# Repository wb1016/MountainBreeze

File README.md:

# Mountain Breeze

> Ergonomics meets Productivity.

## Introduction

"Mountain Breeze" is a tented split mechanical keyboard with a column-staggered layout. With a focus on productivity, Breeze features a full 6x4 alphanumeric layout, arrow keys, and an extra 6 key cluster for typing and coding.

Learn more at: [www.afternoonlabs.com/mountain-breeze](https://www.afternoonlabs.com/mountain-breeze)

## Features

* Tented Split Ergonomics
* Productivity Cluster for Typing and Coding
* Wireless-First, Fits a Giant Battery
* Built-in On/Off Switch
* Open-source PCB design for easy modifications
* Hotswap MX or Choc Sockets, MX Sockets Built-in!
* Diodes Built-in, No Diode Soldering Required
* Columnar Stagger
* Arrow Keys!

## Support us

Enjoying the Breeze? [Buy me a beer](https://www.buymeacoffee.com/Afternoonlabs).

## Contribution

Contributions are encouraged! Whether it's bug fixes, new features, or even simple feedback, everything helps in making the project better.

1. Fork the Project
2. Create your Feature Branch (`git checkout -b feature/SomeFeature`)
3. Commit your Changes (`git commit -m 'Adding SomeFeature'`)
4. Push to the Branch (`git push origin feature/SomeFeature`)
5. Open a Pull Request

## License

Anyone can use this project for personal use. Distributed under the MIT License. See `LICENSE` for more information.

Vendors interested in selling the Breeze, please contact us below.

The use of "Afternoon Labs" is protected under copyright law. Unauthorized use without express permission from "Afternoon Labs", is prohibited.

## Contact

Join our [Discord Server](https://discord.gg/9nsApe3GvG).

Afternoon Labs - [hi@afternoonlabs.com](mailto:hi@afternoonlabs.com)

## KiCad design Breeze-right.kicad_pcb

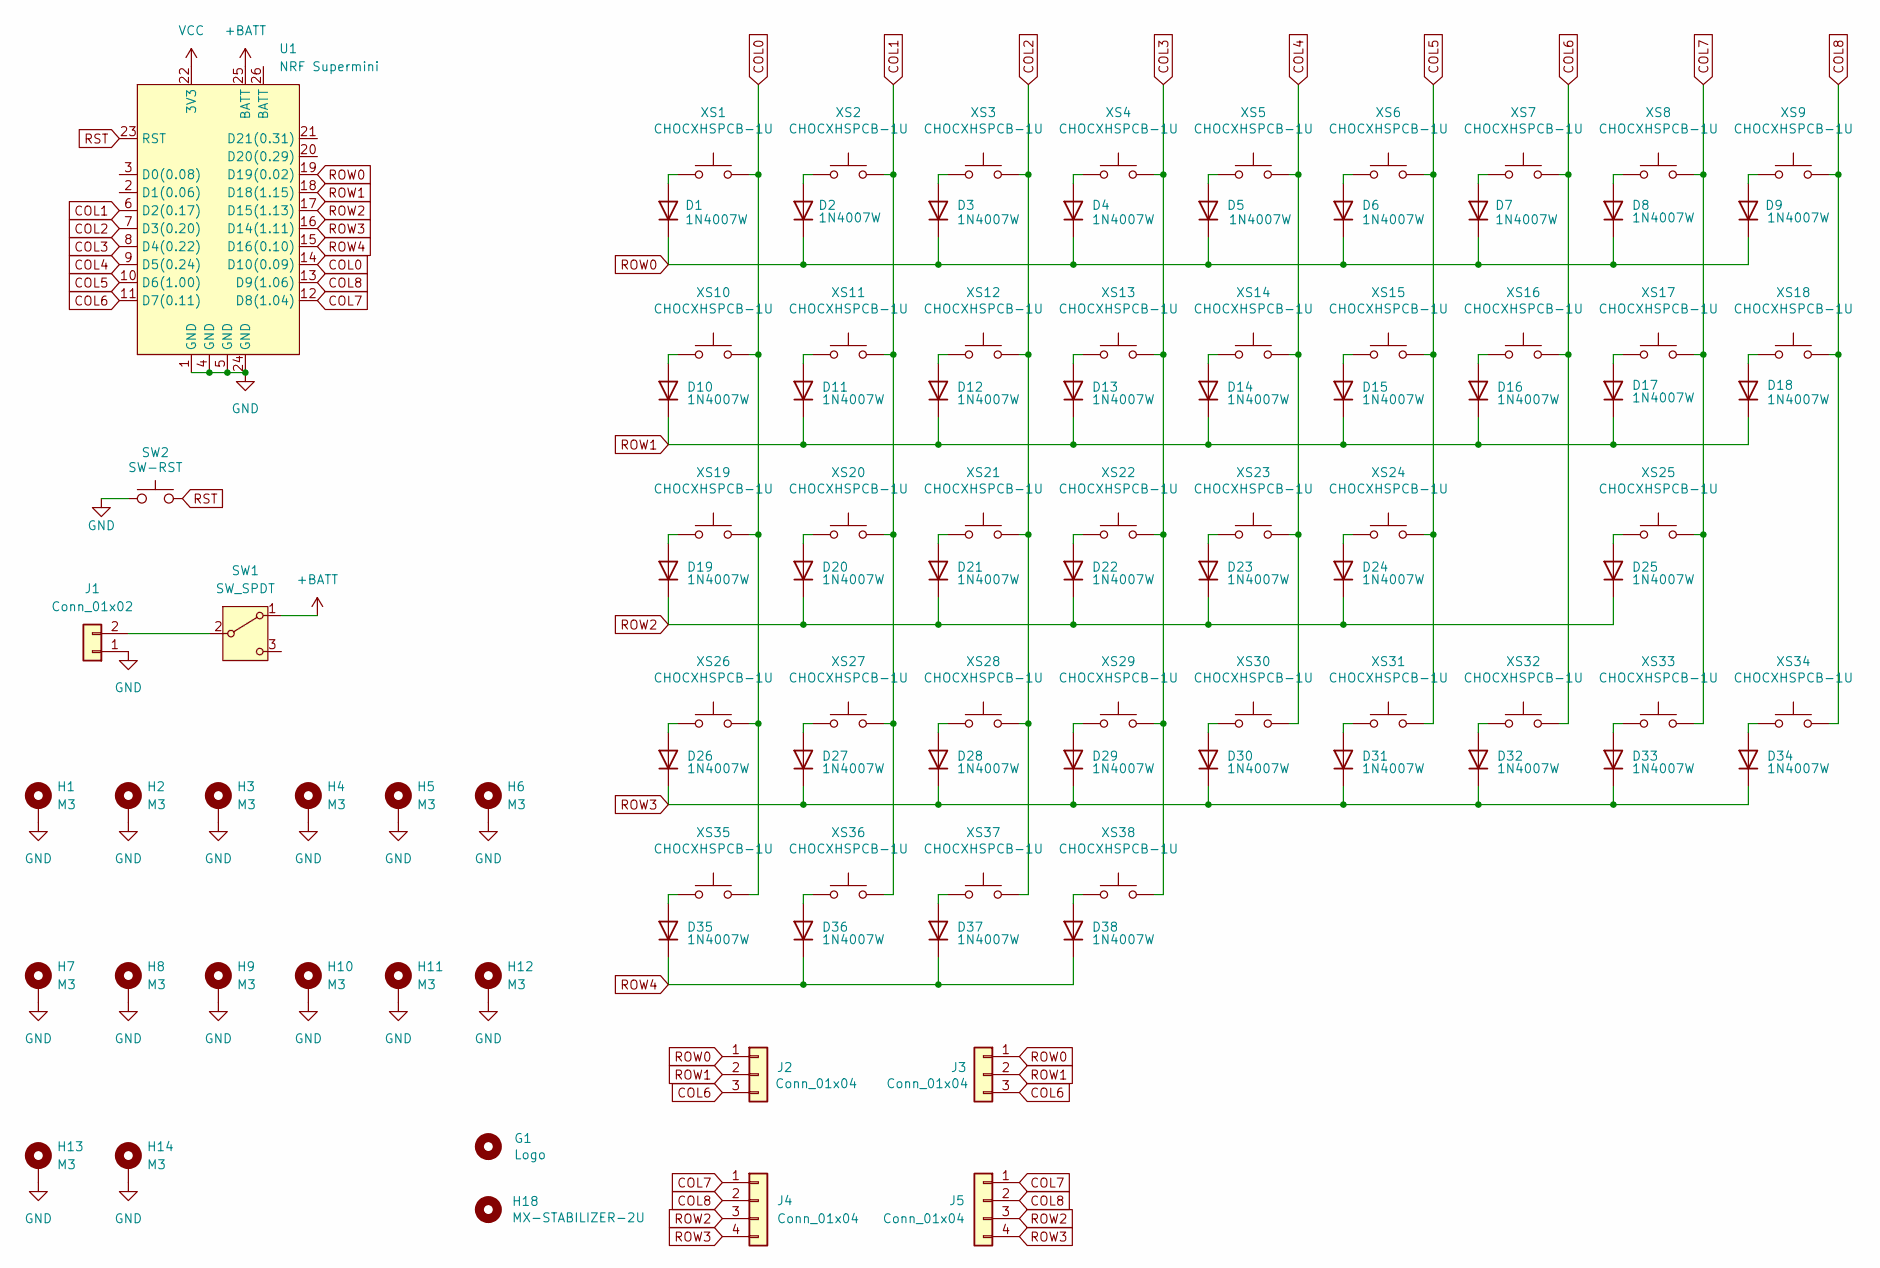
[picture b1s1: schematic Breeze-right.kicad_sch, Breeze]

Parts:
D1, D2, D3, D4, D5, D6, D7, D8, D9, D10, D11, D12, D13, D14, D15, D16, D17, D18, D19, D20, D21, D22, D23, D24, D25, D26, D27, D28, D29, D30, D31, D32, D33, D34, D35, D36, D37, D38: 1N4007W; SOD-123FL_L2.7-W1.8-LS3.7-RD; LCSC C64898
G1: Logo; logo
H1, H3, H4, H6, H7, H9, H10, H11, H12, H13, H14: M3; MountingHole_3.2mm_M3_ISO7380_Pad
H2, H5, H8: M3; MountingHole_3.2mm_M3_ISO7380_Pad_TopOnly
H18: MX-STABILIZER-2U; Stabilizer_MX_2u
J1: Conn_01x02; BATT_PADS
J2, J3: Conn_01x04; PinHeader_1x03_P2.54mm_Vertical
J4, J5: Conn_01x04; PinHeader_1x04_P2.54mm_Vertical
SW1: SW_SPDT; SS12D00; LCSC C145861
SW2: SW-RST; SW_SPST_TL3342; LCSC C2886897
U1: NRF Supermini; NRF_Supermini
XS1, XS2, XS3, XS4, XS5, XS6, XS7, XS8, XS9, XS10, XS11, XS12, XS13, XS14, XS15, XS16, XS17, XS18, XS19, XS20, XS21, XS22, XS23, XS24, XS25, XS26, XS27, XS28, XS29, XS30, XS31, XS32, XS33, XS34, XS35, XS36, XS37, XS38: CHOCXHSPCB-1U; MX_Choc_Hotswap_1-Sided; LCSC C41430893

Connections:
+BATT: SW1.1 (A), U1.25 (BATT)
COL0: U1.14 (D10(0.09)), XS1.2, XS10.2, XS19.2, XS26.2, XS35.2
COL1: U1.6 (D2(0.17)), XS2.2, XS11.2, XS20.2, XS27.2, XS36.2
COL2: U1.7 (D3(0.20)), XS3.2, XS12.2, XS21.2, XS28.2, XS37.2
COL3: U1.8 (D4(0.22)), XS4.2, XS13.2, XS22.2, XS29.2, XS38.2
COL4: U1.9 (D5(0.24)), XS5.2, XS14.2, XS23.2, XS30.2
COL5: U1.10 (D6(1.00)), XS6.2, XS15.2, XS24.2, XS31.2
COL6: J2.3, J3.3, U1.11 (D7(0.11)), XS7.2, XS16.2, XS32.2
COL7: J4.1, J5.1, U1.12 (D8(1.04)), XS8.2, XS17.2, XS25.2, XS33.2
COL8: J4.2, J5.2, U1.13 (D9(1.06)), XS9.2, XS18.2, XS34.2
GND: H1.1, H2.1, H3.1, H4.1, H5.1, H6.1, H7.1, H8.1, H9.1, H10.1, H11.1, H12.1, H13.1, H14.1, J1.1, SW2.1, U1.1 (GND), U1.4 (GND), U1.5 (GND), U1.24 (GND)
unnamed: D1.2 (A), XS1.1
unnamed: D2.2 (A), XS2.1
unnamed: D3.2 (A), XS3.1
unnamed: D4.2 (A), XS4.1
unnamed: D5.2 (A), XS5.1
unnamed: D6.2 (A), XS6.1
unnamed: D7.2 (A), XS7.1
unnamed: D8.2 (A), XS8.1
unnamed: D9.2 (A), XS9.1
unnamed: D10.2 (A), XS10.1
unnamed: D11.2 (A), XS11.1
unnamed: D12.2 (A), XS12.1
unnamed: D13.2 (A), XS13.1
unnamed: D14.2 (A), XS14.1
unnamed: D15.2 (A), XS15.1
unnamed: D16.2 (A), XS16.1
unnamed: D17.2 (A), XS17.1
unnamed: D18.2 (A), XS18.1
unnamed: D19.2 (A), XS19.1
unnamed: D20.2 (A), XS20.1
unnamed: D21.2 (A), XS21.1
unnamed: D22.2 (A), XS22.1
unnamed: D23.2 (A), XS23.1
unnamed: D24.2 (A), XS24.1
unnamed: D25.2 (A), XS25.1
unnamed: D26.2 (A), XS26.1
unnamed: D27.2 (A), XS27.1
unnamed: D28.2 (A), XS28.1
unnamed: D29.2 (A), XS29.1
unnamed: D30.2 (A), XS30.1
unnamed: D31.2 (A), XS31.1
unnamed: D32.2 (A), XS32.1
unnamed: D33.2 (A), XS33.1
unnamed: D34.2 (A), XS34.1
unnamed: D35.2 (A), XS35.1
unnamed: D36.2 (A), XS36.1
unnamed: D37.2 (A), XS37.1
unnamed: D38.2 (A), XS38.1
unnamed: J1.2, SW1.2 (B)
ROW0: D1.1 (K), D2.1 (K), D3.1 (K), D4.1 (K), D5.1 (K), D6.1 (K), D7.1 (K), D8.1 (K), D9.1 (K), J2.1, J3.1, U1.19 (D19(0.02))
ROW1: D10.1 (K), D11.1 (K), D12.1 (K), D13.1 (K), D14.1 (K), D15.1 (K), D16.1 (K), D17.1 (K), D18.1 (K), J2.2, J3.2, U1.18 (D18(1.15))
ROW2: D19.1 (K), D20.1 (K), D21.1 (K), D22.1 (K), D23.1 (K), D24.1 (K), D25.1 (K), J4.3, J5.3, U1.17 (D15(1.13))
ROW3: D26.1 (K), D27.1 (K), D28.1 (K), D29.1 (K), D30.1 (K), D31.1 (K), D32.1 (K), D33.1 (K), D34.1 (K), J4.4, J5.4, U1.16 (D14(1.11))
ROW4: D35.1 (K), D36.1 (K), D37.1 (K), D38.1 (K), U1.15 (D16(0.10))
RST: SW2.2, U1.23 (RST)
VCC: U1.22 (3V3)

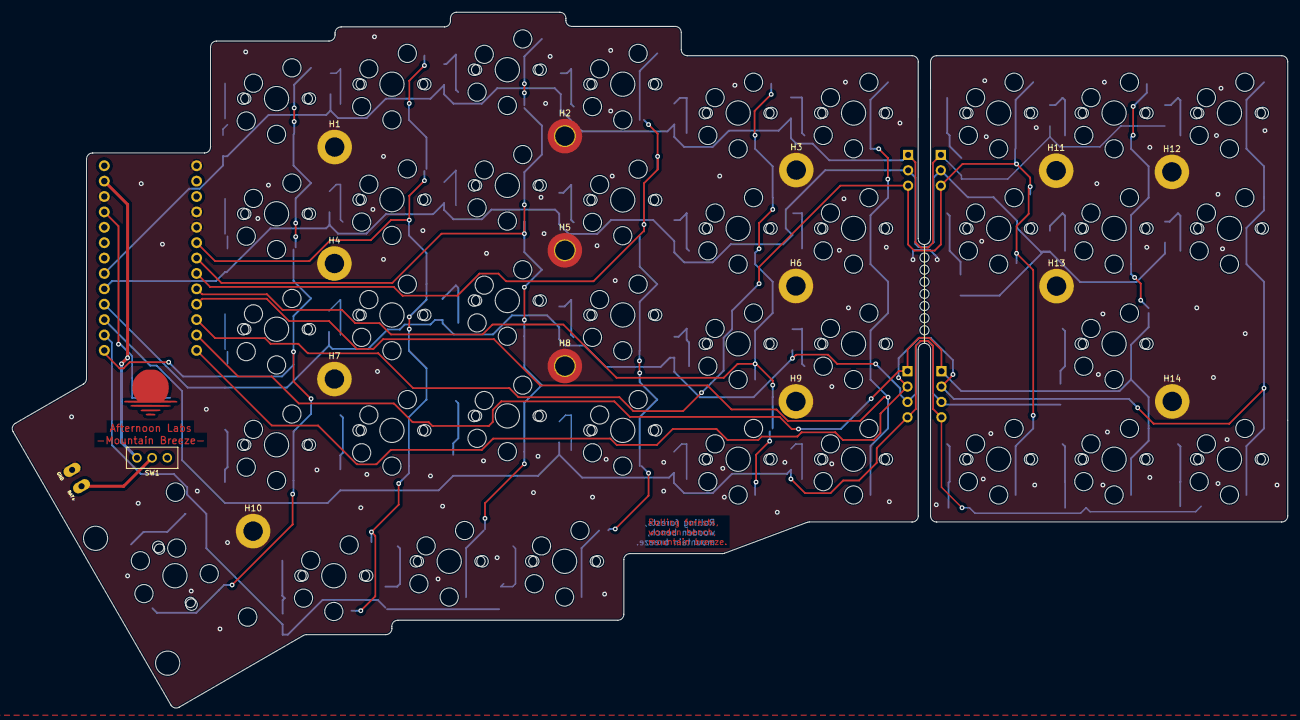
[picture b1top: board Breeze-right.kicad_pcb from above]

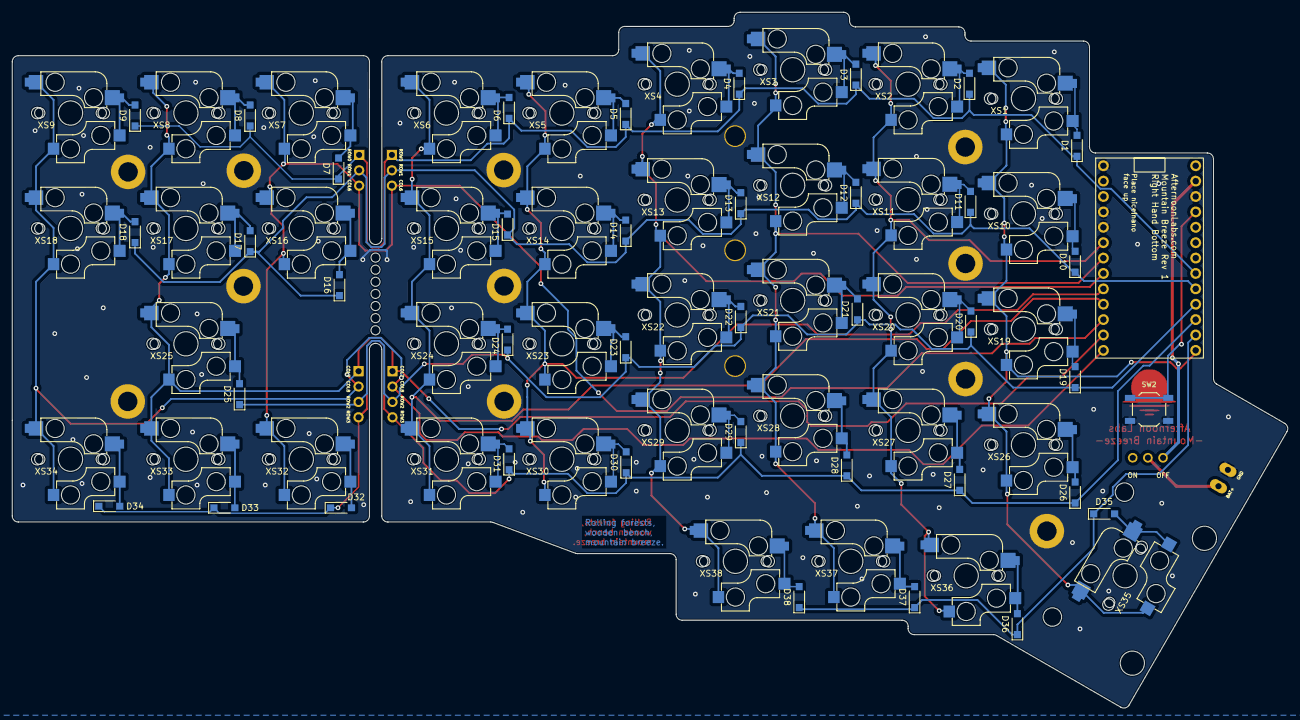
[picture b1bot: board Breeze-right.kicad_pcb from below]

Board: 2 copper layers, 210.6 x 114.9 mm, 100 parts (82 on the bottom side), 56 nets.

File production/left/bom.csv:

Designator,Footprint,Quantity,Value,LCSC Part #
BATT_CONN1,BATT_PADS,1,~,
"D1, D10, D11, D12, D13, D14, D15, D16, D17, D18, D19, D2, D20, D21, D22, D23, D24, D3, D4, D5, D6, D7, D8, D9, DTC1, DTC2, DTC3, DTC4",SOD-123FL,28,DIODE,C64898
"H18, H19, H2, H3, H4, H5, H6, H7, H8, H9",M3-HOLE,10,M3-HOLE,
LGO1,logo,1,Logo,
MCU-MAIN1,ProMicro_1-Sided,1,PRO-MICRO,
PWR1,SS12D00,1,SW_SPDT,C145861
RST1,SW_SPST_TL3342,1,SW-RST,C2886897
STABL1,Stabilizer_MX_2u,1,MX-STABILIZER-2U,
"SW1, SW10, SW11, SW12, SW13, SW14, SW15, SW16, SW17, SW18, SW19, SW2, SW20, SW21, SW22, SW23, SW24, SW3, SW4, SW5, SW6, SW7, SW8, SW9, TC1, TC2, TC3, TC4",MX_Choc_Hotswap_1-Sided,28,CHOCXHSPCB-1U,C41430893

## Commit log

2025-03-26 Rev1.0 Release
2025-09-07 do left
    use gitignore
2025-09-07 untrack
2025-12-01 redo left PCB, redraw supermini symbol
2025-12-12 done
2025-12-15 trace width parity, correct arduino mounting side
2025-12-30 fix mis-named component(xs25)
